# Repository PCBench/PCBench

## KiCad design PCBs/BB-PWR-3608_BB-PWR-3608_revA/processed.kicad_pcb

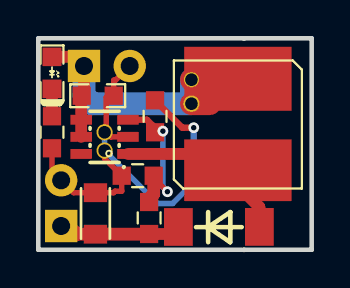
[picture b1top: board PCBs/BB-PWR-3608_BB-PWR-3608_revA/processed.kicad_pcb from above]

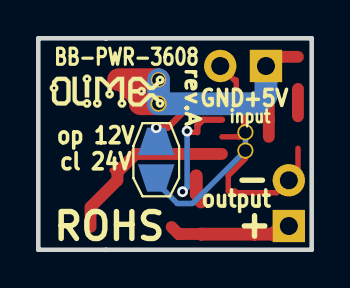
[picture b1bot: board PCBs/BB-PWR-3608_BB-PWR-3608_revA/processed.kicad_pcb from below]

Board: 2 copper layers, 15.2 x 11.8 mm, 18 parts (2 on the bottom side), 7 nets.

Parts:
C1: 22uF/6.3V; C_0603
C3: 22uF/50V; R_0805
D1: LED_RED_0603; LED_0603_KA
D2: 1N5819/SS14; SOD106-R-KA
JP1: Jumper_NO_Small; JUMP_SMD
L1: CL22uH/SD75; SD75
Noname_1: LOGO_OLIMEX_80
P1, P2: HN1x2; HN1x2_Jumper
R1: 39K 1%; R_0603_DWS
R2: 1.05K 1%; R_0603_DWS
R3: 2.2K; R_0603_DWS
R4: 1K 1%; R_0603_DWS
Ref**: Val**; via_09_07
Ref**_2, Ref**_3, Ref**_4: Val**; via_09_07
U1: MT3608; SOT23-6

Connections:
GND: C1.2, C3.2, JP1.2, P1.2, P2.2, R2.2, R3.1, Ref**.0, Ref**_2.0, U1.2
unnamed: C1.1, D1.2, L1.1, P1.1, Ref**_3.0, Ref**_4.0, U1.4, U1.5
unnamed: C3.1, D2.1, P2.1, R1.1
unnamed: D1.1, R3.2
unnamed: D2.2, L1.2, U1.1
unnamed: JP1.1, R4.1
unnamed: R1.2, R2.1, R4.2, U1.3

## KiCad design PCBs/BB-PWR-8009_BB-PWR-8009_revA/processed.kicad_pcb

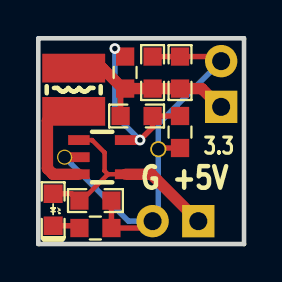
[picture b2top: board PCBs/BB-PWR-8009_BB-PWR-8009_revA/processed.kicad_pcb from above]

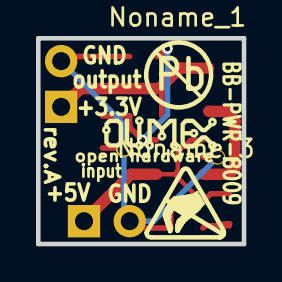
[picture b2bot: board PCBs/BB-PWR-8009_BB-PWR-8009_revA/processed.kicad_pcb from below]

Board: 2 copper layers, 11.4 x 11.4 mm, 17 parts (3 on the bottom side), 6 nets.

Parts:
C1, C3, C4: 22uF/6.3V; C_0603
C2: 22pF; C_0603
D1: LED_RED_0603; LED_0603_KA
L1: 2.2uH/1.5A/JCR<0.1R/CD32; CD32
Noname_1: LOGO_PBFREE
Noname_2: LOGO_OLIMEX_80
Noname_3: LOGO_ANTISTATIC_SMALL_4.5mmX2.8mm
P1, P2: HN1x2; HN1x2_Jumper
R1: 4.99K 1%; R_0603_DWS
R2: 1.1K 1%; R_0603_DWS
R3: 2.2K; R_0603_DWS
Ref**: Val**; via_09_07
Ref**_2: Val**; via_09_07
U1: SY8009AAAC(SOT23-5); SOT-23-5

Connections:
GND: C1.2, C3.2, C4.2, P1.2, P2.2, R2.2, R3.1, Ref**.0, Ref**_2.0, U1.2
unnamed: C1.1, D1.2, P1.1, U1.1, U1.4
unnamed: C2.1, C3.1, C4.1, L1.2, P2.1, R1.1
unnamed: C2.2, R1.2, R2.1, U1.5
unnamed: D1.1, R3.2
unnamed: L1.1, U1.3

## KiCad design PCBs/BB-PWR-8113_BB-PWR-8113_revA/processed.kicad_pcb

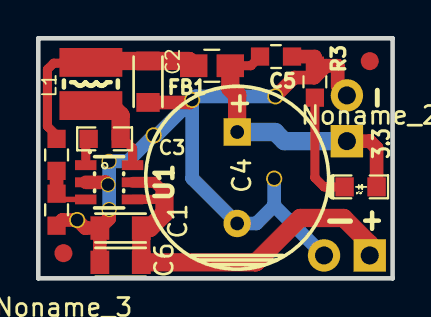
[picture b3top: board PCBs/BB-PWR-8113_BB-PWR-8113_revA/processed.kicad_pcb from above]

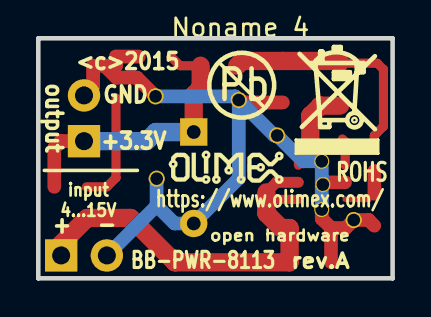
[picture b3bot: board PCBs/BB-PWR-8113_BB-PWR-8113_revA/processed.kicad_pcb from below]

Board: 2 copper layers, 19.7 x 13.3 mm, 28 parts (3 on the bottom side), 8 nets.

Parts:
C1, C6: 2.2uF/50V; R_0805
C2: 22uF/6.3V; R_0805
C3: 100nF; C_0603
C4: 1000uF 6.3V Low ESR; CPOL_200mils_R10mm
C5: 100nF; C_0603_DWS
D1: LED_RED_0603; LED_0603_KA
FB1: FB0805-2A; L0805_5MIL_DWS
L1: 4.7uH/1.5A/JCR<0.1R/CD32; CD32
Noname_1: LOGO_RECYCLEBIN_1
Noname_2, Noname_3: Fiducial1x3_transp
Noname_4: LOGO_PBFREE
Noname_5: LOGO_OLIMEX_80
P1, P2: HN1x2; HN1x2_Jumper
R1: 100K 1%; R_0603_DWS
R2: 22.1K 1%; R_0603_DWS
R3: 2.2K; R_0603_DWS
Ref**: Val**; via_09_07
Ref**_2, Ref**_3, Ref**_4, Ref**_5, Ref**_6, Ref**_7, Ref**_8: Val**; via_09_07
U1: SY8120B1; SOT23-6

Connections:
GND: C1.2, C2.2, C4.2, C5.2, C6.2, P1.2, P2.2, R2.2, R3.1, Ref**.0, Ref**_2.0, Ref**_3.0, Ref**_4.0, Ref**_5.0, Ref**_6.0, Ref**_7.0, Ref**_8.0, U1.2
unnamed: C1.1, C6.1, P1.1, U1.4, U1.5
unnamed: C2.1, FB1.1, L1.2, R1.1
unnamed: C3.1, L1.1, U1.6
unnamed: C3.2, U1.1
unnamed: C4.1, C5.1, D1.2, FB1.2, P2.1
unnamed: D1.1, R3.2
unnamed: R1.2, R2.1, U1.3

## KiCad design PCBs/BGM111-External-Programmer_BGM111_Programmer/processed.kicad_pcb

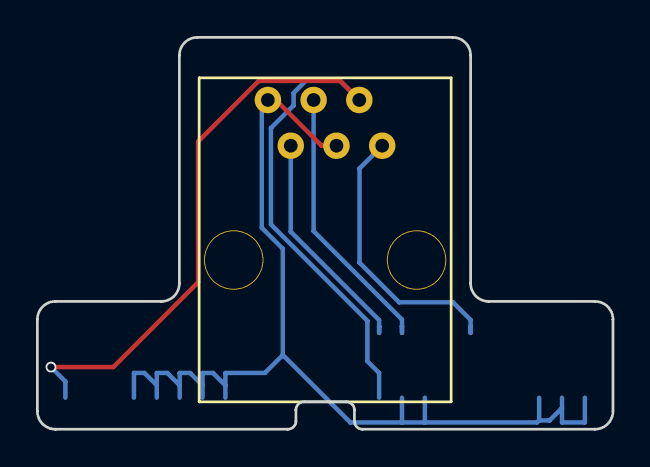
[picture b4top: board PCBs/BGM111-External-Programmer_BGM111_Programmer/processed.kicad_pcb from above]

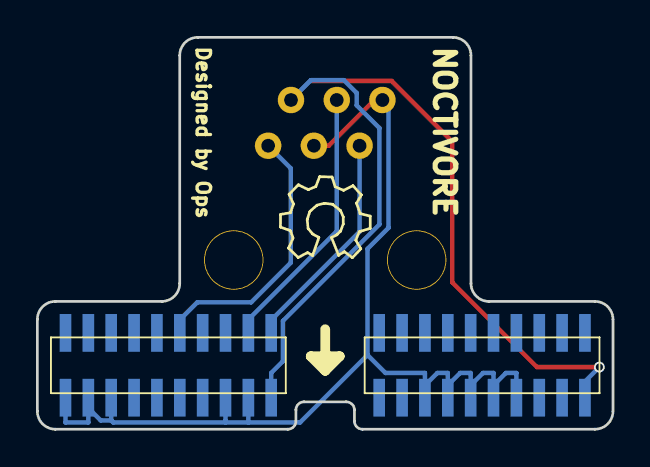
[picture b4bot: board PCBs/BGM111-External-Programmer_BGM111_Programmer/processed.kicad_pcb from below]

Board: 2 copper layers, 32.0 x 21.8 mm, 3 parts (2 on the bottom side), 5 nets.

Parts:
J1: FCI_RJ12; RJ12
P1: Debug Connector; Pin_Header_Straight_2X20_Pitch_1.27mm
P2: Simplicity Connector; Pin_Header_Straight_2X20_Pitch_1.27mm

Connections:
+3V3: J1.5, P1.2, P2.2
/RESET: J1.6, P1.9
/SWCLK: J1.3, P1.3
/SWDIO: J1.2, P1.1
GND: J1.1, J1.4, P1.4, P1.6, P1.16, P1.18, P1.20, P2.8, P2.10, P2.12, P2.14, P2.16

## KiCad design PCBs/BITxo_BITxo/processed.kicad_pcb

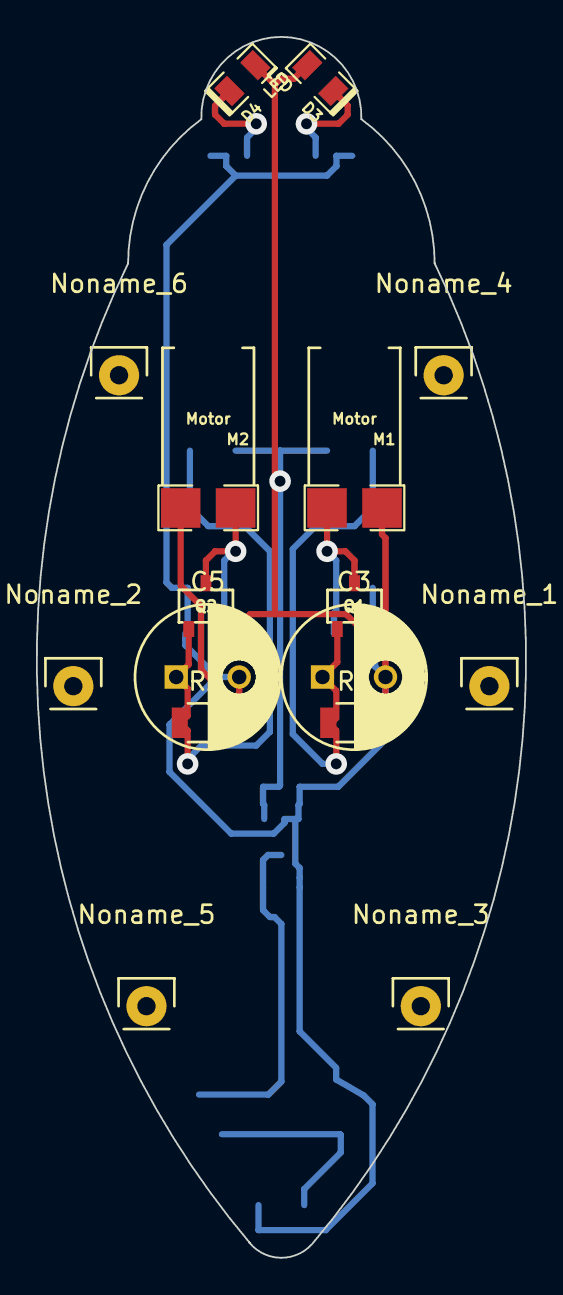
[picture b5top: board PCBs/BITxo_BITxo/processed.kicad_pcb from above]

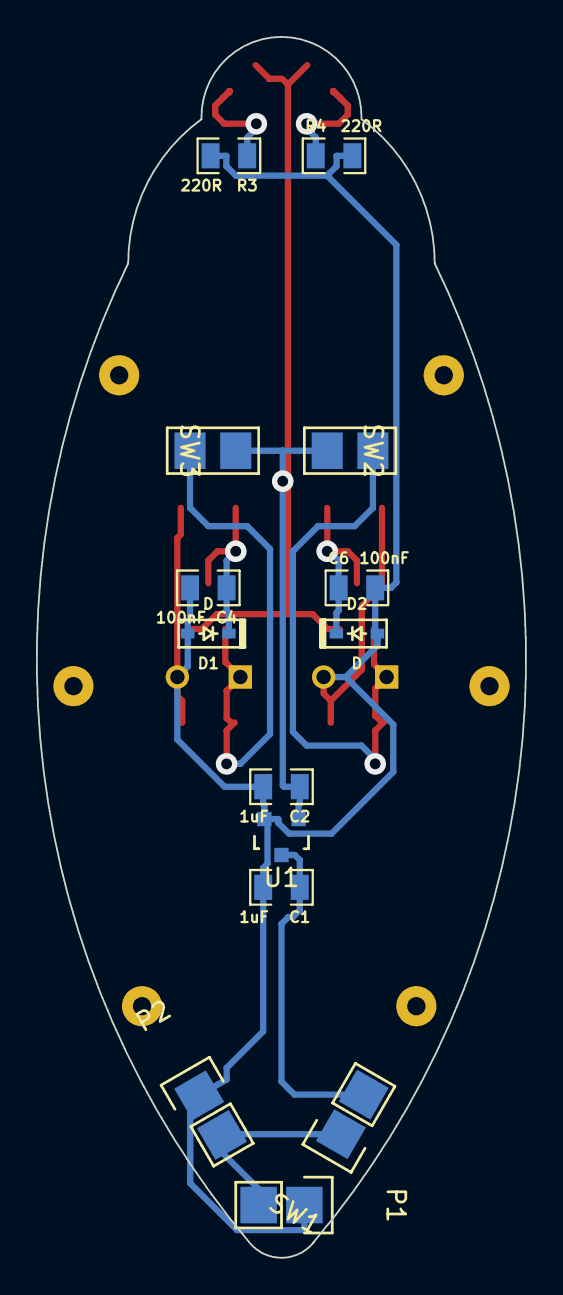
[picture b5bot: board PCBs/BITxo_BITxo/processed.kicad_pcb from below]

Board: 2 copper layers, 27.2 x 67.8 mm, 30 parts (14 on the bottom side), 10 nets.

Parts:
C1, C2: 1uF; SMD0805
C3, C5: 1uF; C_Radial_D8_L11.5_P3.5
C4, C6: 100nF; SMD0805
D1, D2: D; SOD-323
D3, D4: LED; SMD0805_LED
M1, M2: Motor; Vibration_motor
Noname_1, Noname_2, Noname_3, Noname_4, Noname_5, Noname_6: Pin_Header_Straight_1x01
P1: Battery Charger; Pads_1x02
P2: Battery; Pads_1x02
Q1, Q2: P-MOSFET; SOT23-5_MOD_PINOUT
R1, R2: 3M3; R_1206
R3, R4: 220R; SMD0805
SW1: ON/OFF; Pads_1x02
SW2, SW3: Endstop; Pads_Endstop
U1: APE8865NL-30-HF-3; SOT-23

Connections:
+3V3: C2.1, D3.2, D4.2, Q1.3, Q2.3, SW2.2, SW3.2, U1.1
+BATT: P1.2, P2.2, SW1.1
GND: C1.2, C2.2, C3.2, C4.2, C5.2, C6.2, D1.2, D2.2, M1.2, M2.1, P1.1, P2.1, R1.2, R2.2, R3.2, R4.2, U1.2
unnamed: C1.1, SW1.2, U1.3
unnamed: C3.1, Q1.2, R1.1, SW2.3
unnamed: C4.1, D1.1, M1.1, Q1.1
unnamed: C5.1, Q2.2, R2.1, SW3.3
unnamed: C6.1, D2.1, M2.2, Q2.1
unnamed: D3.1, R3.1
unnamed: D4.1, R4.1
